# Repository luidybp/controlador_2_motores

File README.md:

# Projeto de um controlador sensorless microcontrolado para 2 motores CC com alimentação 180 Vcc 

- STM32F411
- Compilador Arm GNU Toolchain
- Cmake
- STlink
- Ninja

- A pasta Gerador PWM é apenas um código teste para gerar sinais em dois canais PWM e um botão que altera a frequência do PWM
- A pasta TCC é efetivamente o código completo

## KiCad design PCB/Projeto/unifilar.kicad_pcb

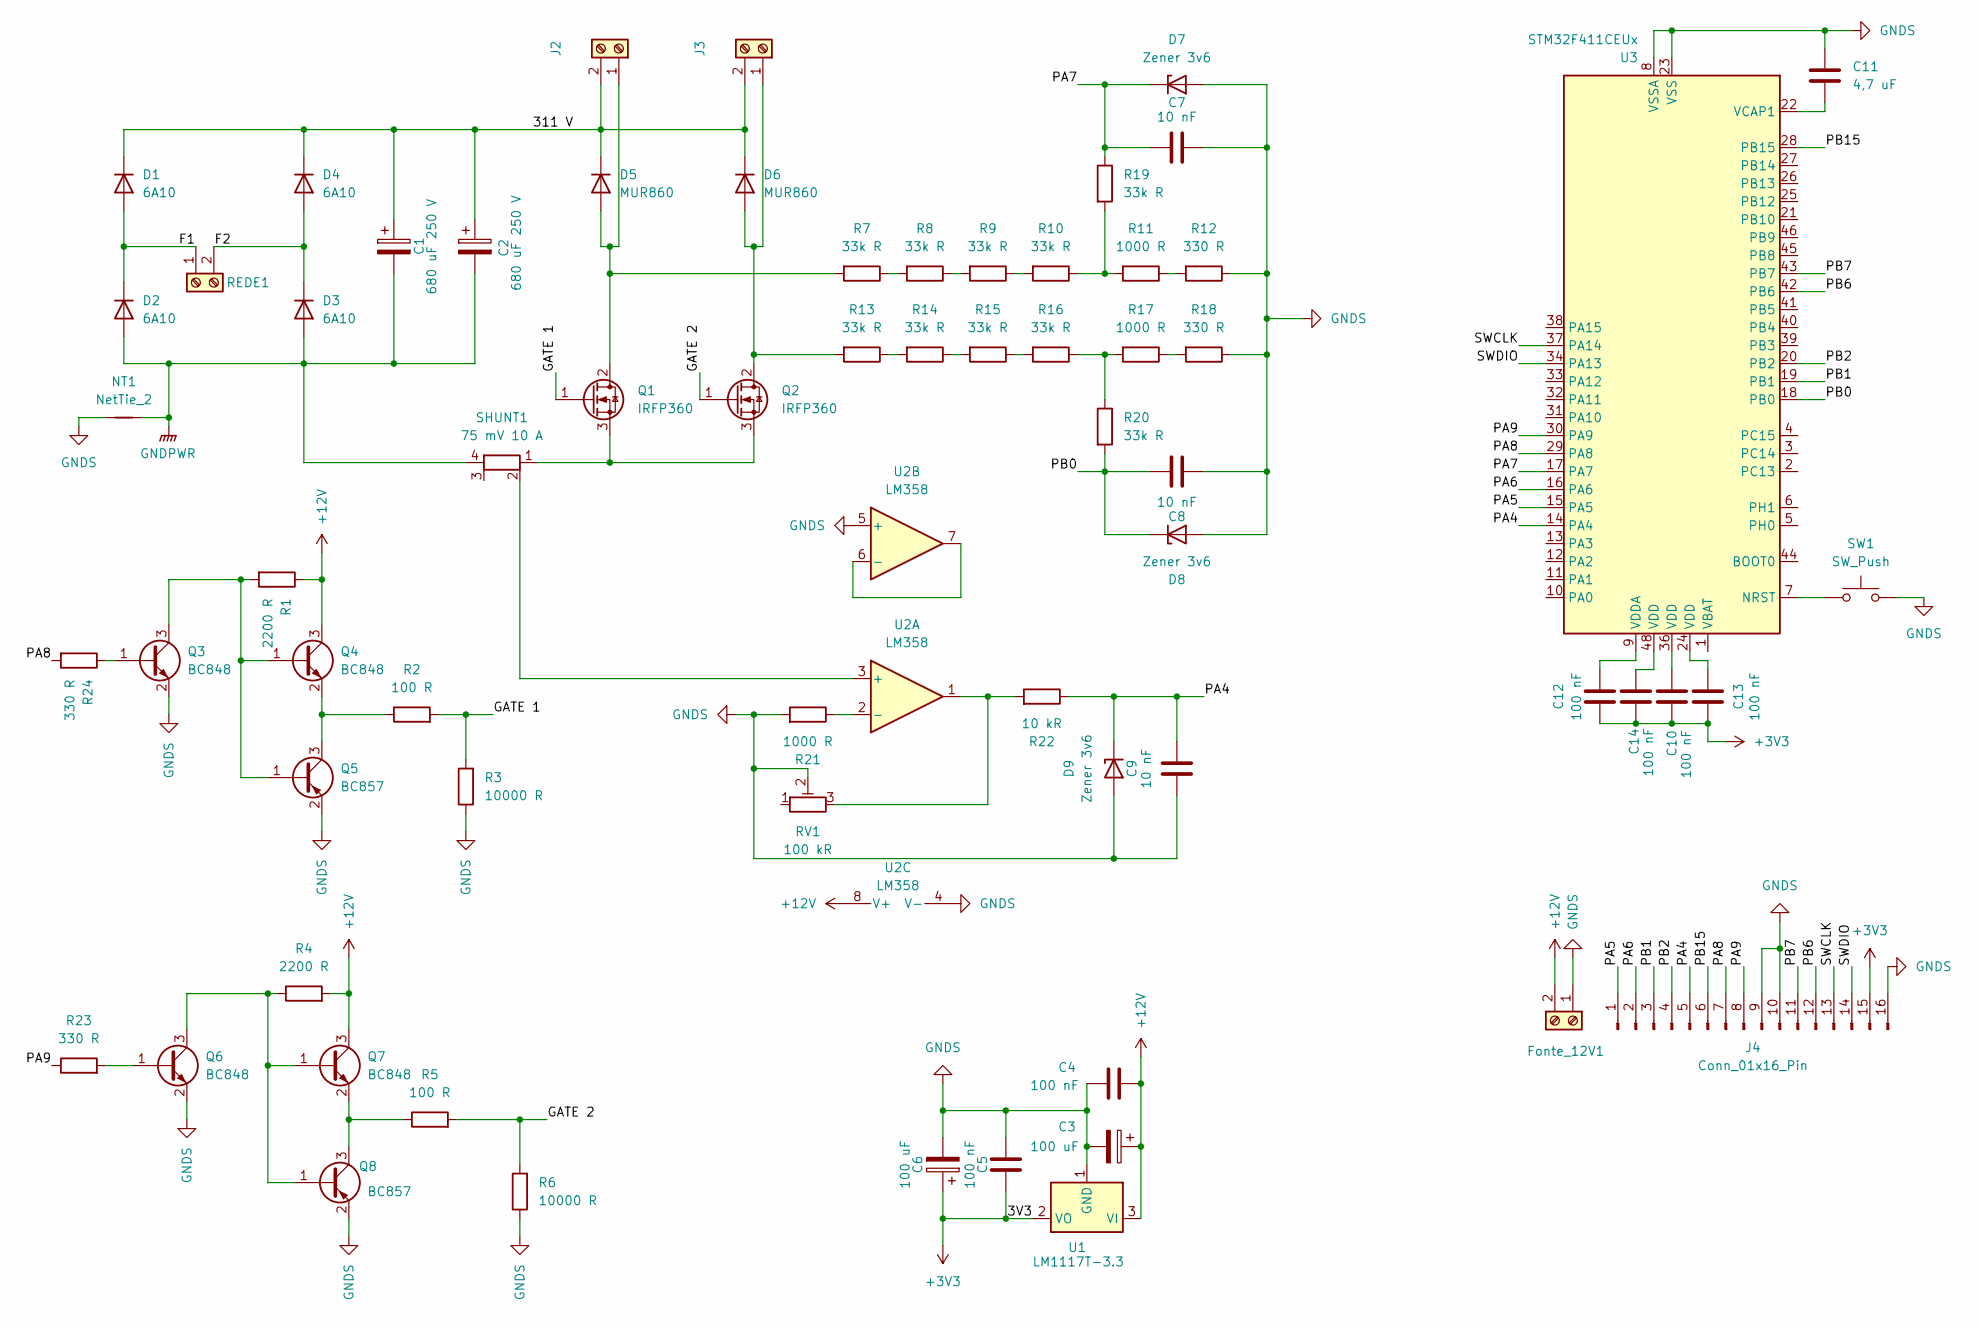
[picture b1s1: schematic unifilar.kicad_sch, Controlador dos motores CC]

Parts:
C1, C2: 680 uF 250 V; CP_Radial_D35.0mm_P10.00mm_SnapIn
C3, C6: 100 uF; CP_Elec_6.3x5.4
C4, C5, C10, C12, C13, C14: 100 nF; C_1206_3216Metric_Pad1.33x1.80mm_HandSolder
C7, C8, C9: 10 nF; C_1206_3216Metric_Pad1.33x1.80mm_HandSolder
C11: 4,7 uF; C_1206_3216Metric_Pad1.33x1.80mm_HandSolder
D1, D2, D3, D4: 6A10; D_5KPW_P12.70mm_Horizontal
D5, D6: MUR860; TO-220-2_Horizontal_TabUp
D7, D8, D9: Zener 3v6; D_SOD-123F
Fonte_12V1: TerminalBlock_Phoenix_MKDS-1,5-2-5.08_1x02_P5.08mm_Horizont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
J2, J3: TerminalBlock_Phoenix_MKDS-1,5-2-5.08_1x02_P5.08mm_Horizont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
J4: Conn_01x16_Pin; PinHeader_1x16_P1.00mm_Horizontal
NT1: NetTie_2; NetTie-2_SMD_Pad0.5mm
Q1, Q2: IRFP360; TO-247-3_Horizontal_TabUp
Q3, Q4, Q6, Q7: BC848; SOT-23
Q5, Q8: BC857; SOT-23
R1, R4: 2200 R; R_1206_3216Metric_Pad1.30x1.75mm_HandSolder
R2, R5: 100 R; R_1206_3216Metric_Pad1.30x1.75mm_HandSolder
R3, R6: 10000 R; R_1206_3216Metric_Pad1.30x1.75mm_HandSolder
R7, R8, R9, R10, R13, R14, R15, R16, R19, R20: 33k R; R_1206_3216Metric_Pad1.30x1.75mm_HandSolder
R11, R17, R21: 1000 R; R_1206_3216Metric_Pad1.30x1.75mm_HandSolder
R12, R18, R23, R24: 330 R; R_1206_3216Metric_Pad1.30x1.75mm_HandSolder
R22: 10 kR; R_1206_3216Metric_Pad1.30x1.75mm_HandSolder
REDE1: TerminalBlock_Phoenix_MKDS-1,5-2-5.08_1x02_P5.08mm_Horizont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
RV1: 100 kR; Potentiometer_Bourns_3296W_Vertical
SHUNT1: 75 mV 10 A; TerminalBlock_Phoenix_MKDS-1,5-4_1x04_P5.00mm_Horizontal
SW1: SW_Push; SW_PUSH_6mm
U1: LM1117T-3.3; TO-220-3_Horizontal_TabUp
U2: LM358
U3: STM32F411CEUx; QFN-48-1EP_7x7mm_P0.5mm_EP5.6x5.6mm

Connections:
+3V3: C5.2, C6.1, C10.1, C12.1, C13.1, C14.1, J4.15, U1.2 (VO)
+12V: C3.1, C4.2, Fonte_12V1.2, Q4.3 (C), Q7.3 (C), R1.1, R4.2, U1.3 (VI), U2.8 (V+)
/311 V: C1.1, C2.1, D1.1 (K), D4.1 (K), D5.1 (K), D6.1 (K), J2.2, J3.2
/F1: D1.2 (A), D2.1 (K), REDE1.1
/F2: D3.1 (K), D4.2 (A), REDE1.2
/GATE 1: Q1.1 (G), R2.2, R3.2
/GATE 2: Q2.1 (G), R5.2, R6.2
/PA4: C9.1, D9.1 (K), J4.5, R22.1, U3.14 (PA4)
/PA5: J4.1, U3.15 (PA5)
/PA6: J4.2, U3.16 (PA6)
/PA7: C7.1, D7.1 (K), R19.1, U3.17 (PA7)
/PA8: J4.7, R24.2, U3.29 (PA8)
/PA9: J4.8, R23.1, U3.30 (PA9)
/PB0: C8.1, D8.1 (K), R20.2, U3.18 (PB0)
/PB1: J4.3, U3.19 (PB1)
/PB2: J4.4, U3.20 (PB2)
/PB6: J4.12, U3.42 (PB6)
/PB7: J4.11, U3.43 (PB7)
/PB15: J4.6, U3.28 (PB15)
/SWCLK: J4.13, U3.37 (PA14)
/SWDIO: J4.14, U3.34 (PA13)
GNDPWR: C1.2, C2.2, D2.2 (A), D3.2 (A), NT1.1, SHUNT1.4
GNDS: C3.2, C4.1, C5.1, C6.2, C7.2, C8.2, C9.2, C11.1, D7.2 (A), D8.2 (A), D9.2 (A), Fonte_12V1.1, J4.9, J4.10, J4.16, NT1.2, Q3.2 (E), Q5.2 (E), Q6.2 (E), Q8.2 (E), R3.1, R6.1, R12.1, R18.1, R21.2, RV1.2, SW1.2, U1.1 (GND), U2.4 (V-), U2.5 (+), U3.8 (VSSA), U3.23 (VSS), U3.35 (VSS), U3.47 (VSS), U3.49 (VSS)
unnamed: C10.2, U3.36 (VDD)
unnamed: C13.2, U3.24 (VDD)
unnamed: C14.2, U3.48 (VDD)
unnamed: D5.2 (A), J2.1, Q1.2 (D), R7.2
unnamed: D6.2 (A), J3.1, Q2.2 (D), R13.2
unnamed: Q1.3 (S), Q2.3 (S), SHUNT1.1
unnamed: Q3.1 (B), R24.1
unnamed: Q3.3 (C), Q4.1 (B), Q5.1 (B), R1.2
unnamed: Q4.2 (E), Q5.3 (C), R2.1
unnamed: Q6.1 (B), R23.2
unnamed: Q6.3 (C), Q7.1 (B), Q8.1 (B), R4.1
unnamed: Q7.2 (E), Q8.3 (C), R5.1
unnamed: R7.1, R8.2
unnamed: R8.1, R9.2
unnamed: R10.1, R11.2, R19.2
unnamed: R9.1, R10.2
unnamed: R11.1, R12.2
unnamed: R13.1, R14.2
unnamed: R14.1, R15.2
unnamed: R15.1, R16.2
unnamed: R16.1, R17.2, R20.1
unnamed: R17.1, R18.2
unnamed: R22.2, RV1.3, U2.1
unnamed: SHUNT1.2, U2.3 (+)
unnamed: R21.1, U2.2 (-)
unnamed: U2.6 (-), U2.7
unnamed: SW1.1, U3.7 (NRST)
unnamed: C11.2, U3.22 (VCAP1)
unnamed: C12.2, U3.9 (VDDA)

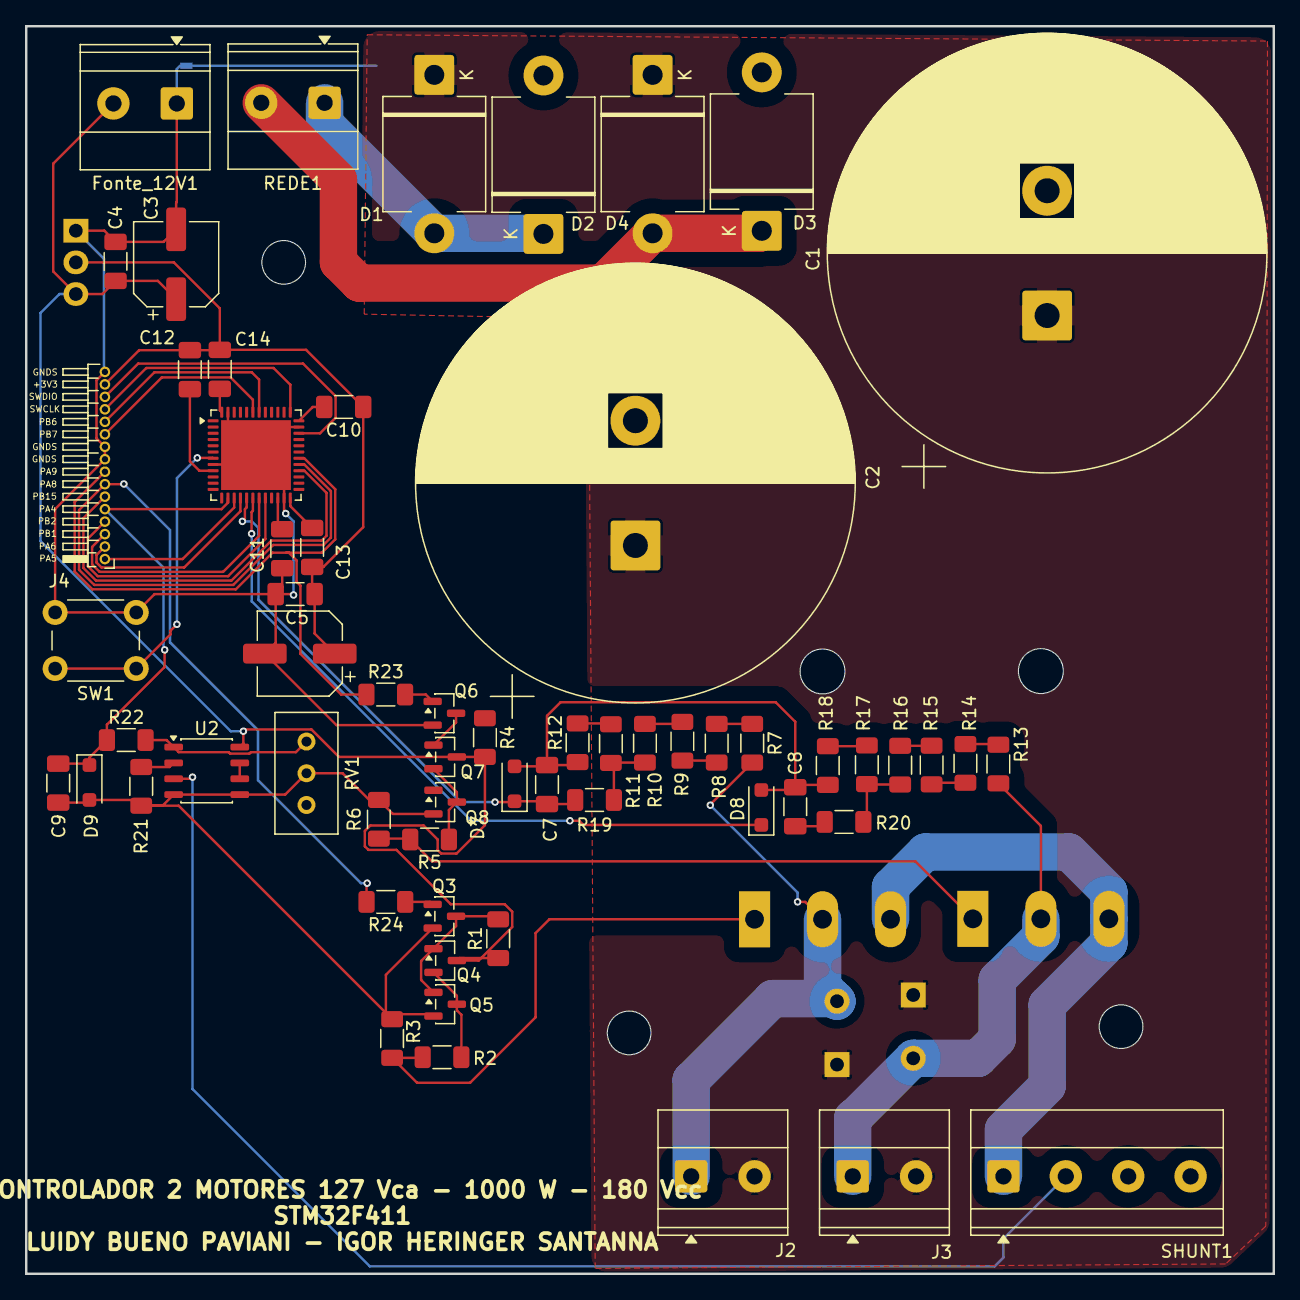
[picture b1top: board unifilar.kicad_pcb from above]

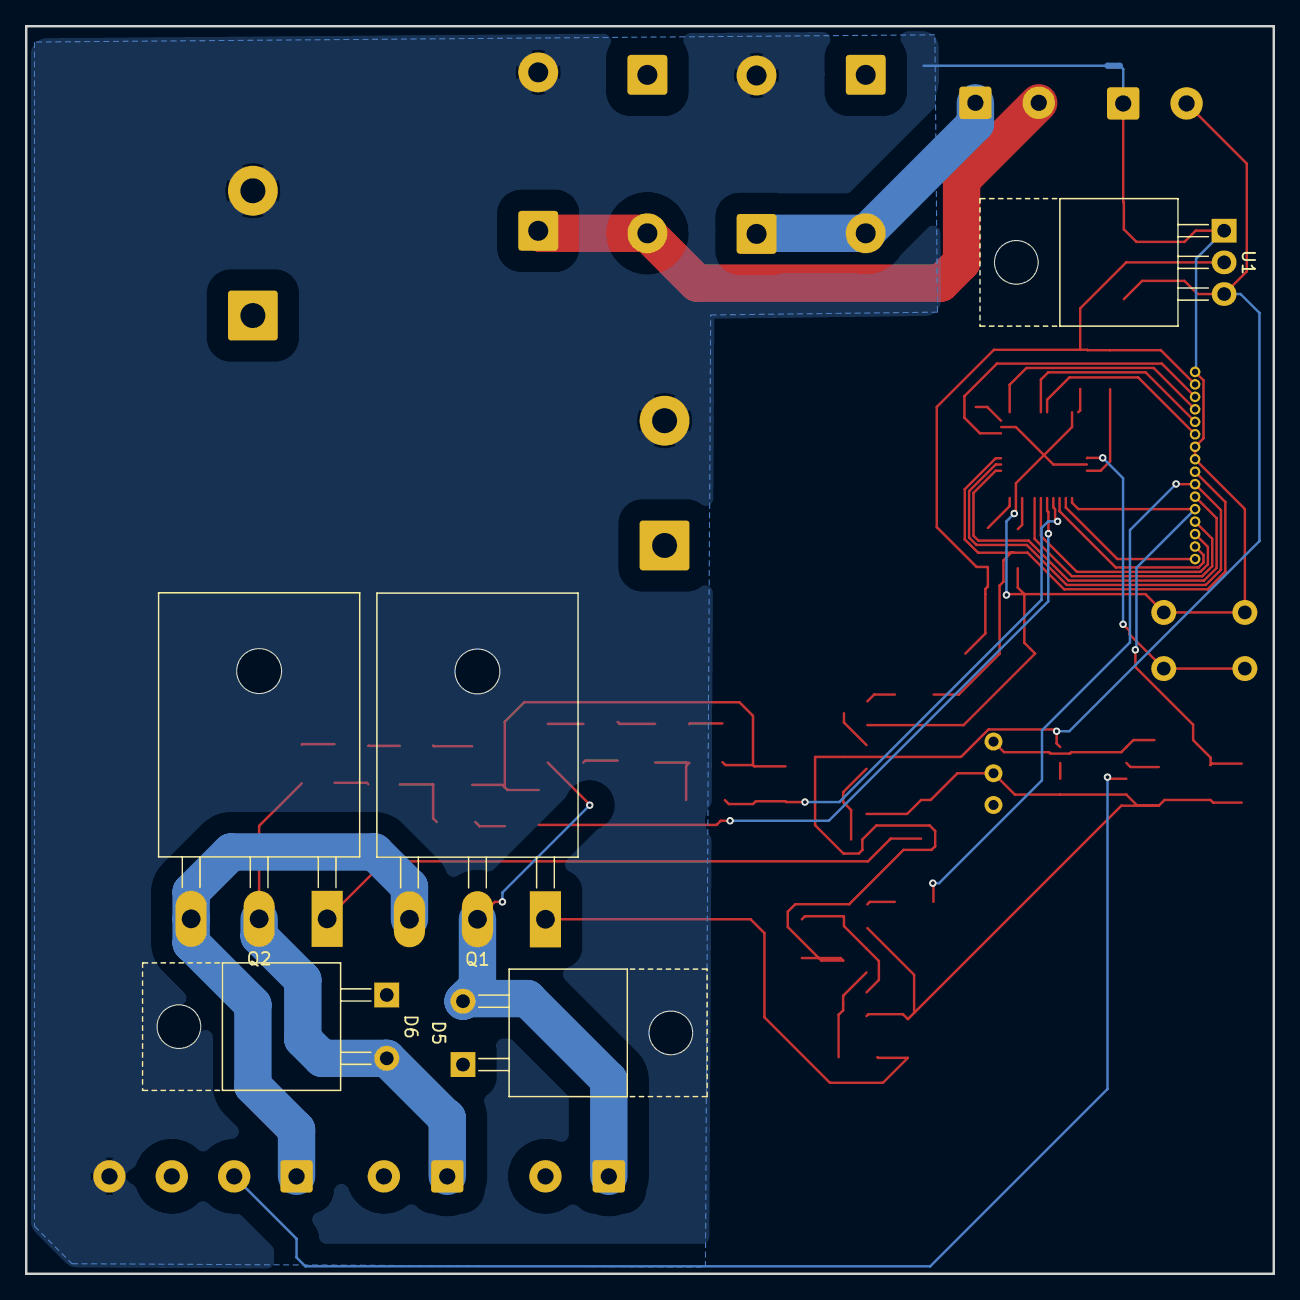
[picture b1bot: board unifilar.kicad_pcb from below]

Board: 2 copper layers, 100.0 x 100.0 mm, 67 parts (6 on the bottom side), 52 nets.

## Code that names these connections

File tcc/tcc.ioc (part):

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Mcu.Name=STM32F411C(C-E)Ux
Mcu.Package=UFQFPN48
Mcu.UserName=STM32F411CEUx
PA13.Mode=Serial_Wire
PA13.Signal=SYS_JTMS-SWDIO
PA14.Mode=Serial_Wire
PA14.Signal=SYS_JTCK-SWCLK
PA4.GPIOParameters=GPIO_Label
PA4.GPIO_Label=shunt
PA4.Signal=ADCx_IN4
PA5.GPIOParameters=GPIO_Label
PA5.GPIO_Label=pot1
PA5.Signal=ADCx_IN5
PA6.GPIOParameters=GPIO_Label
PA6.GPIO_Label=pot2
PA6.Signal=ADCx_IN6
PA7.GPIOParameters=GPIO_Label
PA7.GPIO_Label=emf1
PA7.Signal=ADCx_IN7
PA8.GPIOParameters=GPIO_Label
PA8.GPIO_Label=pwm1
PA8.Signal=S_TIM1_CH1
PA9.GPIOParameters=GPIO_Label
PA9.GPIO_Label=pwm2
PA9.Signal=S_TIM1_CH2
PB0.GPIOParameters=GPIO_Label
PB0.GPIO_Label=emf2
PB0.Signal=ADCx_IN8
PB15.GPIOParameters=GPIO_PuPd,GPIO_Label
PB15.GPIO_Label=bot
PB15.GPIO_PuPd=GPIO_PULLUP
PB15.Signal=GPIO_Input
PC13-ANTI_TAMP.GPIOParameters=GPIO_Label
PC13-ANTI_TAMP.GPIO_Label=debug
PC13-ANTI_TAMP.Signal=GPIO_Output
PH0\ -\ OSC_IN.Mode=HSE-External-Oscillator
PH0\ -\ OSC_IN.Signal=RCC_OSC_IN
PH1\ -\ OSC_OUT.Mode=HSE-External-Oscillator
PH1\ -\ OSC_OUT.Signal=RCC_OSC_OUT
RCC.HSE_VALUE=25000000
RCC.SYSCLKFreq_VALUE=100000000
RCC.SYSCLKSource=RCC_SYSCLKSOURCE_PLLCLK
board=custom
